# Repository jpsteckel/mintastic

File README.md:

# Minstastic: Altoids Tin Meshtastic Node
**Mintastic is a low-cost LoRa meshtastic node built as an**
[**Altoids tin gadget**](https://www.instructables.com/10-Projects-for-Altoids-Tins "Other examples")**.**

## Abstract
**Note: this project is still a work in progress. I plan on updating and finishing this project by early September.**

This project presents the design and implementation of a compact, low-cost Meshtastic mesh networking node packaged in an everyday Altoids tin enclosure. Motivated by the need for a fully standalone node on a campus mesh network, the device integrates a custom PCB featuring an ESP32 microcontroller, SX1262 LoRa transceiver operating at 915 MHz, GPS module, navigation buttons, and LCD display for a custom user interface. Power is supplied by a 3.7 V 1500 mAh LiPo battery with on-board charging circuitry, while an external whip antenna supports long-range communication. <!-- The completed node achieves approximately 6 miles of unobstructed range (mountain-to-mountain) with an average current draw of 0.150 mA. --> The design demonstrates practical RF system integration, efficient power management, and mechanical packaging constraints, resulting in a portable, inexpensive, and self-contained mesh node suitable for campus and outdoor applications.

## 1. Requirements
|  | Requirement |
|--------------------|-------------|
| Power | 3.7V 1500mAh LiPo battery with JST connector, approx 1x2 inches. |
| Size | <58mm width. I've gone with 55x75mm to leave room for battery. |
| Bluetooth | Connects via bluetooth to mobile phone with Meshtastic app |
| GPS | Built-in GPS capability for off-grid use |
| Cost | As cheap as possible for me to prototype, <$50/unit "build it yourself" cost |
| Personal Learning Goals | Learn RF and digital PCB design, and build first highly documented project. |

**Preferred Qualities:**
|  | Goal |
|--------------------|-------------|
| Standalone | Usable without external bluetooth device through built-in user interface |
| Range | ~ 6 mile unobscured |
| Battery Life | >10 hours / <150mA average consumption |

## 2. Design
### Power
The first design concern is being able to both power the board using the LiPo battery, and recharge it. Luckily, most all ESP32, LoRa, and GPS chips support 3.3V VCC, so I only need one regulator chip. I've decided on the **LM2575S-3.3** switching regulator for its efficiency and availability.

For charging and off-board power, I've chosen the **TP4056**, a common charging chip which is powered by 5V via USB-C and outputs 3.7V. This will connect to VBAT which connects to the battery as well as VIN on the regulator.

The circuits surrounding these respective components have been copied mostly from their datasheets.

### MCU
Mintastic will use an ESP32 due to their native bluetooth features. Most could handle this job, I have chosen the **ESP32 S3 N16R8**. Although it costs slightly more than other modules, its large flash memory gives me a lot of room to add features in the future without needing to upgrade hardware.

**Full MCU Pinout**
| ESP32 Pin | Connection | Pulled high/low/NA |
| - | - | - |
| EN | Reset Button | High |
| IO0 | Boot Button | High |
| IO1 | Battery Divider | |
| IO2 | User Button | High |
| IO3 | User Button | High |
| IO4 | GPS Reset | High |
| IO5 | GPS On/Off | High |
| IO6 | User Button | High |
| IO7 | User Button | High |
| IO8 | LoRa SCK | |
| IO9 | LoRa MISO | |
| IO10 | LoRa MOSI | |
| IO11 | LCD Reset | |
| IO12 | LCD SDA | |
| IO13 | LCD SCL | |
| IO14 | LCD CS | |
| IO15 | LCD DC | |
| IO16 | User Button | High |
| IO17 | GPS Tx | |
| IO18 | GPS Rx | |
| USB+ | USB D+ | |
| USB- | USB D- | |
| IO38 | LoRa RF Switch | |
| IO39 | LoRa DIO1 | |
| IO40 | LoRa Busy | |
| IO41 | LoRa NSS | |
| IO42 | LoRa Reset | |
| IO46 | | unconnected/low |
| IO48 | Red LED | |

Note: The periferal connections were decided (mostly) arbitrarily or based on firmware defaults.

All other pins are unconnected.

### Periferals
#### I. LoRa Module
The Semtech SX1262 is the LoRa IC used almost universally for Mesh nodes. For simplicity, I will use the [**Wio-SX1262**](https://wiki.seeedstudio.com/wio_sx1262/) module by Seeed Studio. This compact module features an onboard filter, switch, and IPEX connector, making it ideal for this. (I will be using a separate SMA connector rather than the IPEX for LoRa.)

#### II. GPS Module
I do not want to be reliant on a mobile phone's internet connection for location information, so I plan to use an on-board GPS chip. I've selected the cheap chinese [**ATGM336H**](https://www.alldatasheet.com/html-pdf/2250270/ZHONGKE/ATGM336H/2443/7/ATGM336H.html) module to support GPS for this module.

#### III. 2.4 Inch TFT LCD Display
I've selected a generic ST7789 display for this with a built-in controller. I will simply connect it through a 1x8 pin socket.

### PCB
To fit design constraints, I've set the width of the PCB to be just under the inner lip diameter of the Altoids tin, 55mm, and its height to be ~ 40 mm less than the length of the tin, 75mm, to leave room for the battery. I've also rounded 2 of the board's edges to match the curvature of the tin.

To lower costs, I've decided to use a 2-layer board over a simpler 4-layer design. For this reason, I will need to separate UHF from digital signals so that they can have a solid ground plane beneath each trace.

The dielectric between the layers is far too thick for impedance controlled microstrip traces, so I will use the GCPW (Grounded Coplanar Waveguide) technique.

**Impedance control**

To calculate impedance values, I am using an [online calculator](https://impedancecalculator.com/). 
UHF signal traces will need to be impedance controlled to 50 Ohms. Using GCPW, this requires a 1 mm trace and 0.2 mm gap. This gets us down to 55.7 Ohms, resulting in 0.556 dB/inch loss at 900 MHz. Close enough for this ~0.1 inch line.

I've determined the microstrip traces to have a reasonable impedance for digital signals.

### UI Design

## 3. Manufacturing
Prototype fabricated through JLCPCB. All components were ordered through AliExpress. I assembled the PCB myself using SMT tools at UD.

**Prototype cost breakdown:**
| Item | Cost ($) | Note |
| ---- | ---- | ---- |
| PCB | 4.95 | 24.75/5, includes shipping |
| [Capacitors](https://www.aliexpress.com/item/3256810330121955.html?spm=a2g0o.order_list.order_list_main.10.21ef1802iwNV2p) | 0.20 | 3.19/320 * 20 |
| [Resistors](https://www.aliexpress.com/item/3256810577510361.html?spm=a2g0o.order_list.order_list_main.32.21ef1802iwNV2p) | 0.07 | 2.37/660 * 19 |
| [Inductors](https://www.aliexpress.com/item/3256808828460642.html?spm=a2g0o.order_list.order_list_main.78.21ef1802iwNV2p) | 0.03 | 4.35/300 * 0.029 |
| [LEDs](https://www.aliexpress.com/item/2251800651687366.html?spm=a2g0o.order_list.order_list_main.114.21ef1802iwNV2p) | 0.05 | 1.51/100 * 3 |
| [Resettable Fuses](https://www.aliexpress.com/item/3256805049615392.html?spm=a2g0o.order_list.order_list_main.44.21ef1802iwNV2p) | 0.33 | 3.32/20 * 2 |
| [SS14 Diode](https://www.aliexpress.com/item/3256806391314857.html?spm=a2g0o.order_list.order_list_main.26.21ef1802iwNV2p) | 0.03 | 1.47/50 |
| [IN5819 Diode](https://www.aliexpress.com/item/3256801365779334.html?spm=a2g0o.order_list.order_list_main.425.21ef1802iwNV2p) | 0.02 | 0.91/50
| [USB-C Connector](https://www.aliexpress.com/item/3256804454151365.html?spm=a2g0o.order_list.order_list_main.435.21ef1802iwNV2p) | 0.22 | 2.19/10 |
| [Battery JST connector](https://www.aliexpress.com/item/3256807568732637.html?spm=a2g0o.order_list.order_list_main.102.21ef1802iwNV2p) | 0.09 | 1.77/20 |
| [LiPo Battery](https://www.aliexpress.com/item/3256808031709894.html?spm=a2g0o.order_list.order_list_main.84.21ef1802iwNV2p) | 6.73 | |
| [TP4056](https://www.aliexpress.com/item/2251832528051428.html?spm=a2g0o.order_list.order_list_main.96.21ef1802iwNV2p) | 0.10 | 0.94/10 |
| [LM2575S-3.3](https://www.aliexpress.com/item/3256806770889152.html?spm=a2g0o.order_list.order_list_main.50.21ef1802iwNV2p) | 0.28 | 5.54/20 |
| [ESP32-S3-N16R8](https://www.aliexpress.com/item/3256806005505510.html?spm=a2g0o.order_list.order_list_main.90.21ef1802iwNV2p) | 4.79 | |
| [WIO-SX1262](https://www.aliexpress.com/item/3256808235584580.html?spm=a2g0o.order_list.order_list_main.451.21ef1802iwNV2p) | 4.97 | |
| [ATGM336H](https://www.aliexpress.com/item/3256804828510067.html?spm=a2g0o.order_list.order_list_main.66.21ef1802iwNV2p) | 3.04 | |
| [IPEX connector](https://www.aliexpress.com/item/3256801185019750.html?spm=a2g0o.order_list.order_list_main.108.21ef1802iwNV2p) | 0.15 | 1.50/10 |
| [SMA connector](https://www.aliexpress.com/item/3256807238600626.html?spm=a2g0o.order_list.order_list_main.475.21ef1802iwNV2p) | 0.77 | 3.86/5  |
| [SMA Cable](https://www.aliexpress.com/item/3256803838912502.html?spm=a2g0o.order_list.order_list_main.38.21ef1802iwNV2p) | 2.34 | |
| [2.4in TFT LCD Display](https://www.aliexpress.com/item/3256811879116899.html?spm=a2g0o.order_list.order_list_main.125.21ef1802iwNV2p) | 5.57 | |
| [8-pin socket](https://www.aliexpress.com/item/3256804056304729.html?spm=a2g0o.order_list.order_list_main.72.21ef1802iwNV2p) | 0.19 | 1.94/10 |
| [2-pin headers](https://www.aliexpress.com/item/3256807300285852.html?spm=a2g0o.order_list.order_list_main.140.21ef1802iwNV2p) | 0.05 | 1.63/180 * 5 |
| [Push Buttons](https://www.aliexpress.com/item/3256808033339761.html?spm=a2g0o.order_list.order_list_main.510.21ef1802iwNV2p) | 0.05 | 0.99/100 * 5 |
| [UHF Whip Antenna](https://www.aliexpress.us/item/3256804421300249.html) | 4.60 | |
| [GPS Antenna](https://www.aliexpress.com/item/2251832500323977.html?spm=a2g0o.order_list.order_list_main.20.21ef1802iwNV2p) | 1.59 | |
| Altoids tin | 0.00 | Everyone has one somewhere
| Total | 41.20 | |

Note on above calculations: This is a rough estimate of how much each unit costs at a small scale to self-assemble. Many components, such as resistors, I had to buy in kits. In these cases, I took the cost of the kit, divided it by the total number of pieces included, and multiplied by the number of that component per unit. $40 is about the lowest you will find a mesh node for on Amazon, so this is a reasonable cost. It goes without saying that I would use PCBA for production at scale, but for this project it would have cost ~$193.

## 4. Measurement Setup
...

## 5. Results
| Spec | Target | Simulated | Measured |
| ---- | ------ | --------- | -------- |
|
[Plots]

## 6. Discussion & Lessons Learned
...

## 7. Conclusion
...

## References
I was inspired by Martin Held's [Altoids tin CW radio](https://www.youtube.com/watch?v=zBLEqTVUgEY&list=WL&index=7&pp=iAQBsAgC) project.

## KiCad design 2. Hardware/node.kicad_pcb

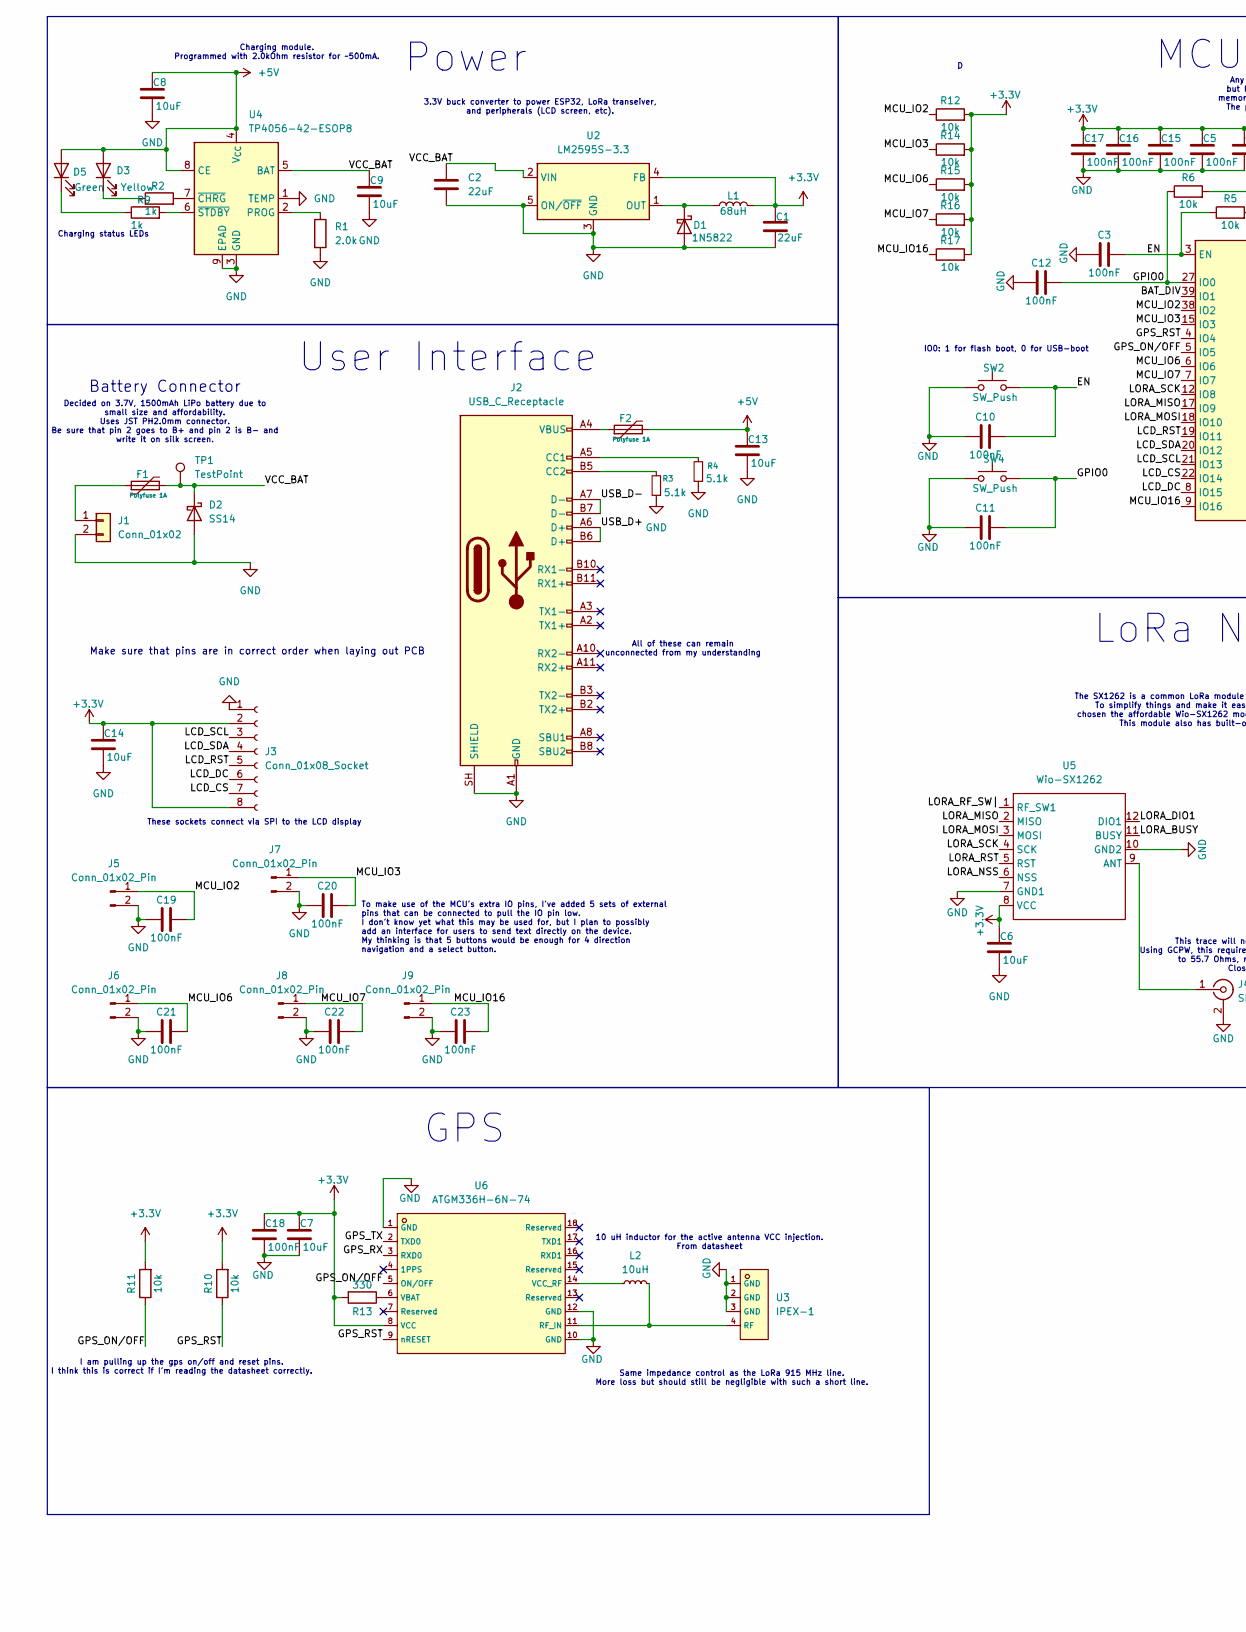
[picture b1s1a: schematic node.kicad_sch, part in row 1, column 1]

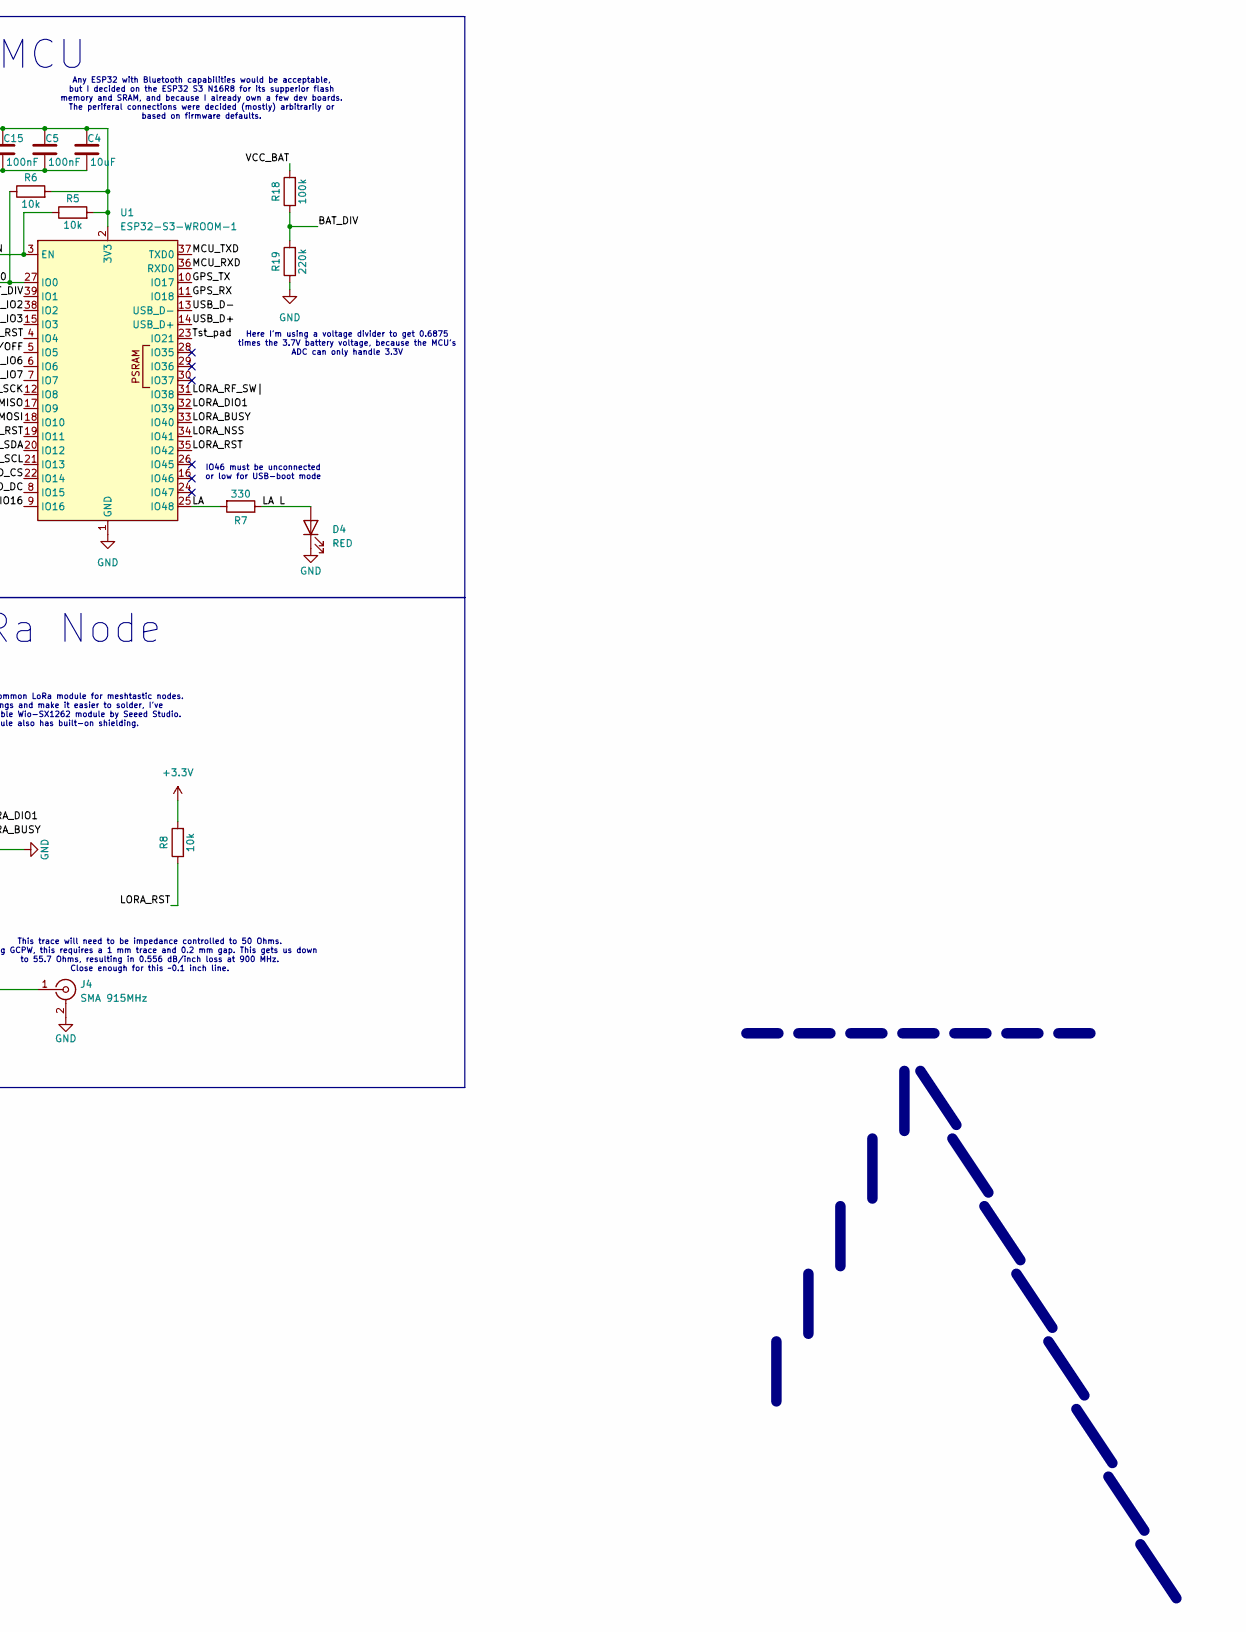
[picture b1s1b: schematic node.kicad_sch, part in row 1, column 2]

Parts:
C1, C2: 22uF; C_0603_1608Metric
C3, C5, C10, C11, C12, C15, C16, C17, C18, C19, C20, C21, C22, C23: 100nF; C_0603_1608Metric
C4, C6, C7, C8, C9, C13, C14: 10uF; C_0603_1608Metric
D1: 1N5822; D_DO-201AD_P15.24mm_Horizontal
D2: SS14; D_SMA
D3: Yellow; LED_0805_2012Metric
D4: RED; LED_0805_2012Metric
D5: Green; LED_0805_2012Metric
F1, F2: Polyfuse 1A; Fuse_0805_2012Metric
J1: Conn_01x02; JST_PH_B2B-PH-K_1x02_P2.00mm_Vertical
J2: USB_C_Receptacle; USB_C_Receptacle_HRO_TYPE-C-31-M-12
J3: Conn_01x08_Socket; PinHeader_1x08_P2.54mm_Vertical
J4: SMA 915MHz; SMA_BAT_Wireless_BWSMA-KWE-Z001
J5, J6, J7, J8, J9: Conn_01x02_Pin; PinHeader_1x02_P2.54mm_Vertical
L1: 68uH; L_0603_1608Metric
L2: 10uH; L_0603_1608Metric
R1: 2.0k; R_0201_0603Metric
R2, R9: 1k; R_0201_0603Metric
R3, R4: 5.1k; R_0201_0603Metric
R5, R6, R8, R10, R11, R12, R14, R15, R16, R17: 10k; R_0603_1608Metric
R7, R13: 330; R_0603_1608Metric
R18: 100k; R_0805_2012Metric
R19: 220k; R_0805_2012Metric
SW2, SW4: SW_Push; SW_SPST_PTS645Sx43SMTR92
TP1: TestPoint; TestPoint_Pad_D2.5mm
U1: ESP32-S3-WROOM-1
U2: LM2595S-3.3; TO-263-5_TabPin3
U3: IPEX-1; C2987682_IPEX-SMD_4P-L2_6-W2_6-LS3_0; LCSC C2987682
U4: TP4056-42-ESOP8; SOIC-8-1EP_3.9x4.9mm_P1.27mm_EP2.41x3.3mm_ThermalVias
U5: Wio-SX1262; MODULE12P-1.27-11X11.6MM; MPN Wio-SX1262
U6: ATGM336H-6N-74; C5804601_COMM-SMD_18P-L10_1-W9_7-P1_1-TL_L76-LB; LCSC C5804601

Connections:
+3.3V: C1.1, C4.1, C5.1, C6.1, C7.1, C14.1, C15.1, C16.1, C17.1, C18.1, J3.2, J3.8, L1.2, R5.2, R6.2, R8.2, R10.2, R11.2, R12.2, R13.2, R14.2, R15.2, R16.2, R17.2, U1.2 (3V3), U2.4 (FB), U5.8 (VCC), U6.8 (VCC)
+5V: C8.1, C13.1, D3.2 (A), D5.2 (A), F2.2, U4.4 (V_{CC}), U4.8 (CE)
/BAT_DIV: R18.1, R19.2, U1.39 (IO1)
/EN: C3.2, C10.2, R5.1, SW2.2, U1.3 (EN)
/GPIO0: C11.2, C12.2, R6.1, SW4.2, U1.27 (IO0)
/GPS_ON/OFF: R11.1, U1.5 (IO5), U6.5 (ON/OFF)
/GPS_RST: R10.1, U1.4 (IO4), U6.9 (nRESET)
/GPS_RX: U1.11 (IO18), U6.3 (RXD0)
/GPS_TX: U1.10 (IO17), U6.2 (TXD0)
/LA: R7.2, U1.25 (IO48)
/LA L: D4.2 (A), R7.1
/LCD_CS: J3.7, U1.22 (IO14)
/LCD_DC: J3.6, U1.8 (IO15)
/LCD_RST: J3.5, U1.19 (IO11)
/LCD_SCL: J3.3, U1.21 (IO13)
/LCD_SDA: J3.4, U1.20 (IO12)
/LORA_BUSY: U1.33 (IO40), U5.11 (BUSY)
/LORA_DIO1: U1.32 (IO39), U5.12 (DIO1)
/LORA_MISO: U1.17 (IO9), U5.2 (MISO)
/LORA_MOSI: U1.18 (IO10), U5.3 (MOSI)
/LORA_NSS: U1.34 (IO41), U5.6 (NSS)
/LORA_RF_SW|: U1.31 (IO38), U5.1 (RF_SW1)
/LORA_RST: R8.1, U1.35 (IO42), U5.5 (RST)
/LORA_SCK: U1.12 (IO8), U5.4 (SCK)
/MCU_IO2: C19.2, J5.1, R12.1, U1.38 (IO2)
/MCU_IO3: C20.2, J7.1, R14.1, U1.15 (IO3)
/MCU_IO6: C21.2, J6.1, R15.1, U1.6 (IO6)
/MCU_IO7: C22.2, J8.1, R16.1, U1.7 (IO7)
/MCU_IO16: C23.2, J9.1, R17.1, U1.9 (IO16)
/MCU_RXD: U1.36 (RXD0)
/MCU_TXD: U1.37 (TXD0)
/Tst_pad: U1.23 (IO21)
/USB_D+: J2.A6 (D+), J2.B6 (D+), U1.14 (USB_D+)
/USB_D-: J2.A7 (D-), J2.B7 (D-), U1.13 (USB_D-)
/VCC_BAT: C2.1, C9.1, D2.1 (K), F1.2, R18.2, TP1.1 (1_1), U2.2 (VIN), U4.5 (BAT)
GND: C1.2, C2.2, C3.1, C4.2, C5.2, C6.2, C7.2, C8.2, C9.2, C10.1, C11.1, C12.1, C13.2, C14.2, C15.2, C16.2, C17.2, C18.2, C19.1, C20.1, C21.1, C22.1, C23.1, D1.2 (A), D2.2 (A), D4.1 (K), J1.2, J2.A1 (GND), J2.A12 (GND), J2.B1 (GND), J2.B12 (GND), J2.SH (SHIELD), J3.1, J4.2 (Ext), J5.2, J6.2, J7.2, J8.2, J9.2, R1.2, R3.1, R4.1, R19.1, SW2.1, SW4.1, U1.1 (GND), U1.40 (GND), U1.41 (GND), U2.3 (GND), U2.5 (ON/~OFF), U3.1 (GND), U3.2 (GND), U3.3 (GND), U4.1 (TEMP), U4.3 (GND), U4.9 (EPAD), U5.7 (GND1), U5.10 (GND2), U6.1 (GND), U6.10 (GND), U6.12 (GND)
unnamed: D1.1 (K), L1.1, U2.1 (OUT)
unnamed: D3.1 (K), R2.1
unnamed: D5.1 (K), R9.1
unnamed: F2.1, J2.A4 (VBUS), J2.A9 (VBUS), J2.B4 (VBUS), J2.B9 (VBUS)
unnamed: F1.1, J1.1
unnamed: J2.A5 (CC1), R4.2
unnamed: J2.B5 (CC2), R3.2
unnamed: J4.1 (In), U5.9 (ANT)
unnamed: L2.2, U3.4 (RF), U6.11 (RF_IN)
unnamed: R1.1, U4.2 (PROG)
unnamed: R2.2, U4.7 (~CHRG)
unnamed: R9.2, U4.6 (~STDBY)
unnamed: R13.1, U6.6 (VBAT)
unnamed: L2.1, U6.14 (VCC_RF)

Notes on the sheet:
User Interface
Here I'm using a voltage divider to get 0.6875 times the 3.7V battery voltage, because the MCU's ADC can only handle 3.3V
Power
The SX1262 is a common LoRa module for meshtastic nodes. To simplify things and make it easier to solder, I've chosen the affordable Wio-SX1262 module by Seeed Studio. This module also has built-on shielding.
These sockets connect via SPI to the LCD display
Make sure that pins are in correct order when laying out PCB
IO46 must be unconnected or low for USB-boot mode
GPS
MCU
3.3V buck converter to power ESP32, LoRa transeiver, and peripherals (LCD screen, etc).
LoRa Node
Same impedance control as the LoRa 915 MHz line. More loss but should still be negligible with such a short line.
Battery Connector
------- |\ | \ | \ | \ | \ \ \ \
All of these can remain unconnected from my understanding
This trace will need to be impedance controlled to 50 Ohms. Using GCPW, this requires a 1 mm trace and 0.2 mm gap. This gets us down to 55.7 Ohms, resulting in 0.556 dB/inch loss at 900 MHz. Close enough for this ~0.1 inch line.
I am pulling up the gps on/off and reset pins. I think this is correct if I'm reading the datasheet correctly.
Charging module. Programmed with 2.0kOhm resistor for ~500mA.
To make use of the MCU's extra IO pins, I've added 5 sets of external pins that can be connected to pull the IO pin low. I don't know yet what this may be used for, but I plan to possibly add an interface for users to send text directly on the device. My thinking is that 5 buttons would be enough f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
Any ESP32 with Bluetooth capabilities would be acceptable, but I decided on the ESP32 S3 N16R8 for its supperior flash memory and SRAM, and because I already own a few dev boards. The periferal connections were decided (mostly) arbitrarily or based on firmware defaults.
Charging status LEDs
Decided on 3.7V, 1500mAh LiPo battery due to small size and affordability. Uses JST PH2.0mm connector. Be sure that pin 2 goes to B+ and pin 2 is B- and write it on silk screen.
IO0: 1 for flash boot, 0 for USB-boot
10 uH inductor for the active antenna VCC injection. From datasheet

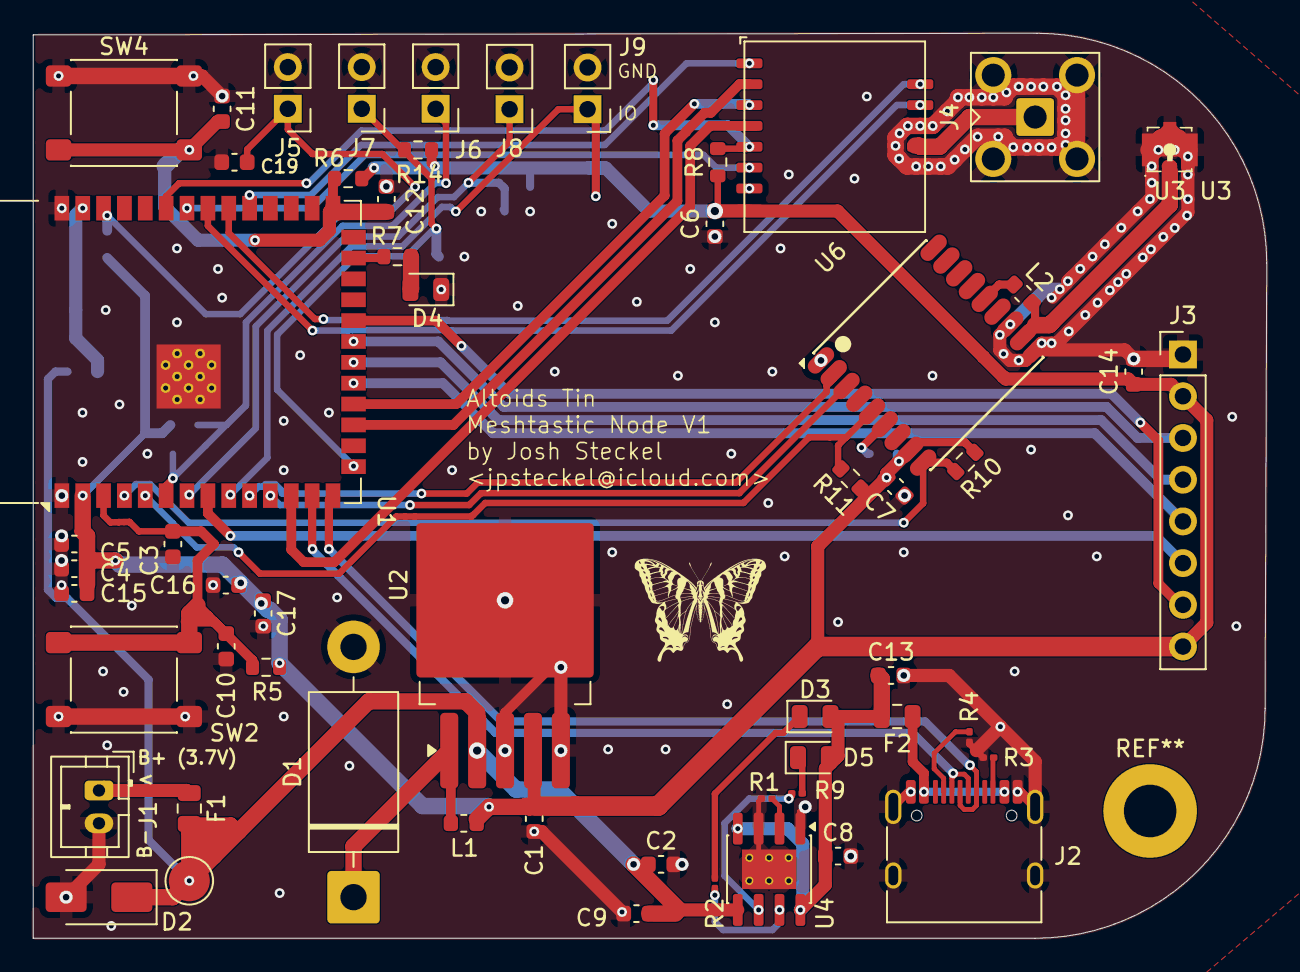
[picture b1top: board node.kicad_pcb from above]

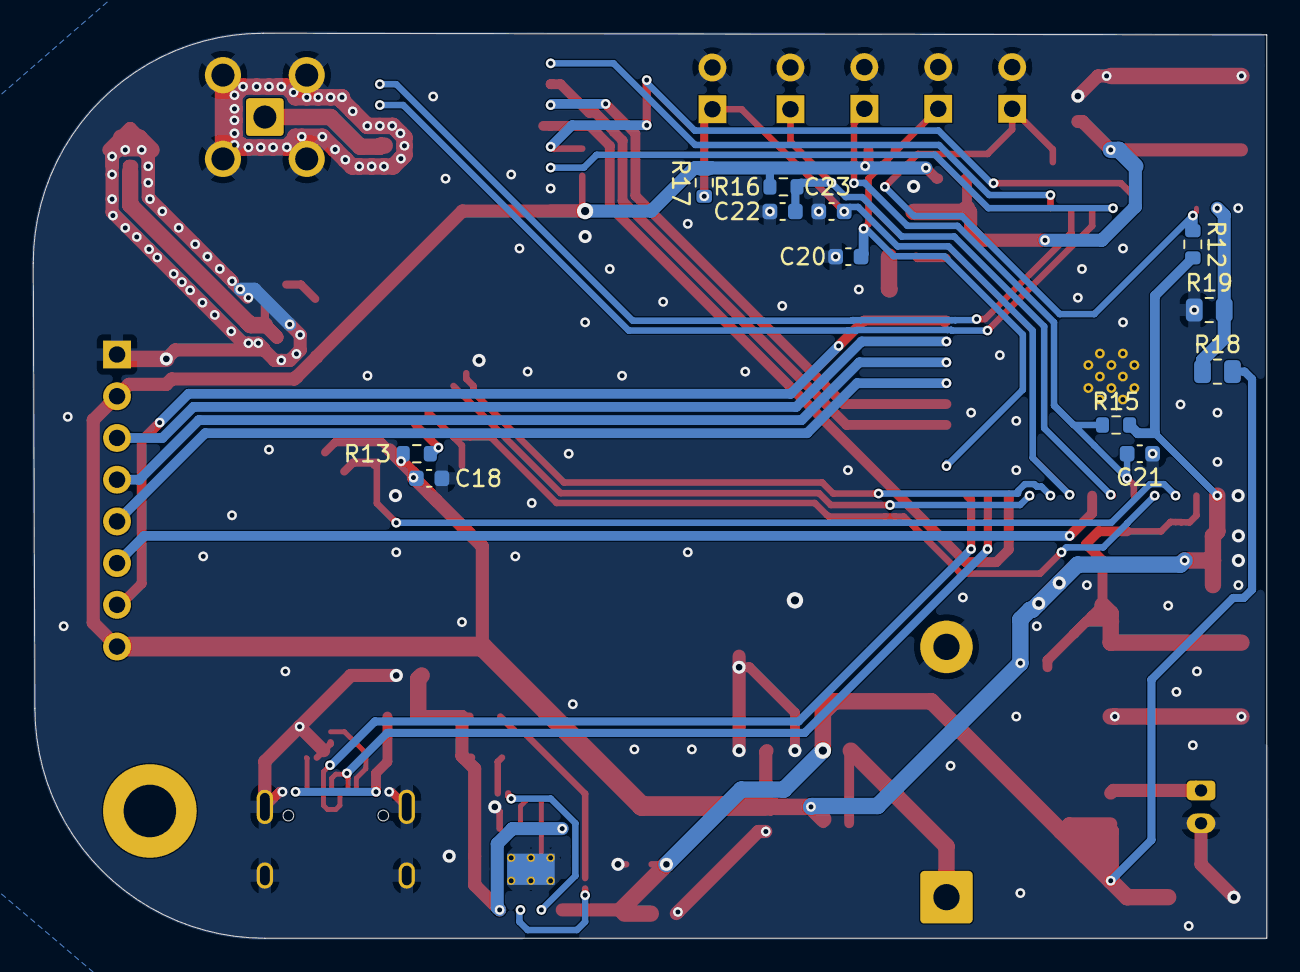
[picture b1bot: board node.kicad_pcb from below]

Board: 2 copper layers, 75.1 x 55.1 mm, 69 parts (12 on the bottom side), 47 nets.

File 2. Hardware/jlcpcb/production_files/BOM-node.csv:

Comment,Designator,Footprint,LCSC,Quantity
100k,R18,R_0805_2012Metric,C149504,1
100nF,"C10,C11,C12,C15,C16,C17,C18,C19,C20,C21,C22,C23,C3,C5",C_0603_1608Metric,C14663,14
10k,"R10,R11,R12,R14,R15,R16,R17,R5,R6,R8",R_0603_1608Metric,C29718,10
10uF,"C13,C14,C4,C6,C7,C8,C9",C_0603_1608Metric,C19702,7
10uH,L2,L_0603_1608Metric,C1035,1
1k,"R2,R9",R_0201_0603Metric,C21190,2
2.0k,R1,R_0201_0603Metric,C22975,1
220k,R19,R_0805_2012Metric,C17556,1
22uF,"C1,C2",C_0603_1608Metric,C59461,2
330,"R13,R7",R_0603_1608Metric,C23138,2
5.1k,"R3,R4",R_0201_0603Metric,C23186,2
68uH,L1,L_0603_1608Metric,C13415,1
ATGM336H-6N-74,U6,C5804601_COMM-SMD_18P-L10_1-W9_7-P1_1-TL_L76-LB,C5804601,1
Green,D5,LED_0805_2012Metric,C2297,1
IPEX-1,U3,C2987682_IPEX-SMD_4P-L2_6-W2_6-LS3_0,C2987682,1
Polyfuse 1A,"F1,F2",Fuse_0805_2012Metric,C269104,2
RED,D4,LED_0805_2012Metric,C84256,1
SS14,D2,D_SMA,C7420316,1
TP4056-42-ESOP8,U4,SOIC-8-1EP_3.9x4.9mm_P1.27mm_EP2.41x3.3mm_ThermalVias,C16581,1
Yellow,D3,LED_0805_2012Metric,C2296,1
USB_C_Receptacle,J2,USB_C_Receptacle_HRO_TYPE-C-31-M-12,,1
Conn_01x08_Socket,J3,PinHeader_1x08_P2.54mm_Vertical,,1
Wio-SX1262,U5,MODULE12P-1.27-11X11.6MM,,1
LM2595S-3.3,U2,TO-263-5_TabPin3,,1
ESP32-S3-WROOM-1,U1,ESP32-S3-WROOM-1,,1
TestPoint,TP1,TestPoint_Pad_D2.5mm,,1
SW_Push,SW4,SW_SPST_PTS645Sx43SMTR92,,1
SW_Push,SW2,SW_SPST_PTS645Sx43SMTR92,,1
SMA 915MHz,J4,SMA_BAT_Wireless_BWSMA-KWE-Z001,,1
Conn_01x02,J1,JST_PH_B2B-PH-K_1x02_P2.00mm_Vertical,,1
1N5822,D1,D_DO-201AD_P15.24mm_Horizontal,,1
Conn_01x02_Pin,J9,PinHeader_1x02_P2.54mm_Vertical,,1
Conn_01x02_Pin,J8,PinHeader_1x02_P2.54mm_Vertical,,1
Conn_01x02_Pin,J7,PinHeader_1x02_P2.54mm_Vertical,,1
Conn_01x02_Pin,J6,PinHeader_1x02_P2.54mm_Vertical,,1
Conn_01x02_Pin,J5,PinHeader_1x02_P2.54mm_Vertical,,1
